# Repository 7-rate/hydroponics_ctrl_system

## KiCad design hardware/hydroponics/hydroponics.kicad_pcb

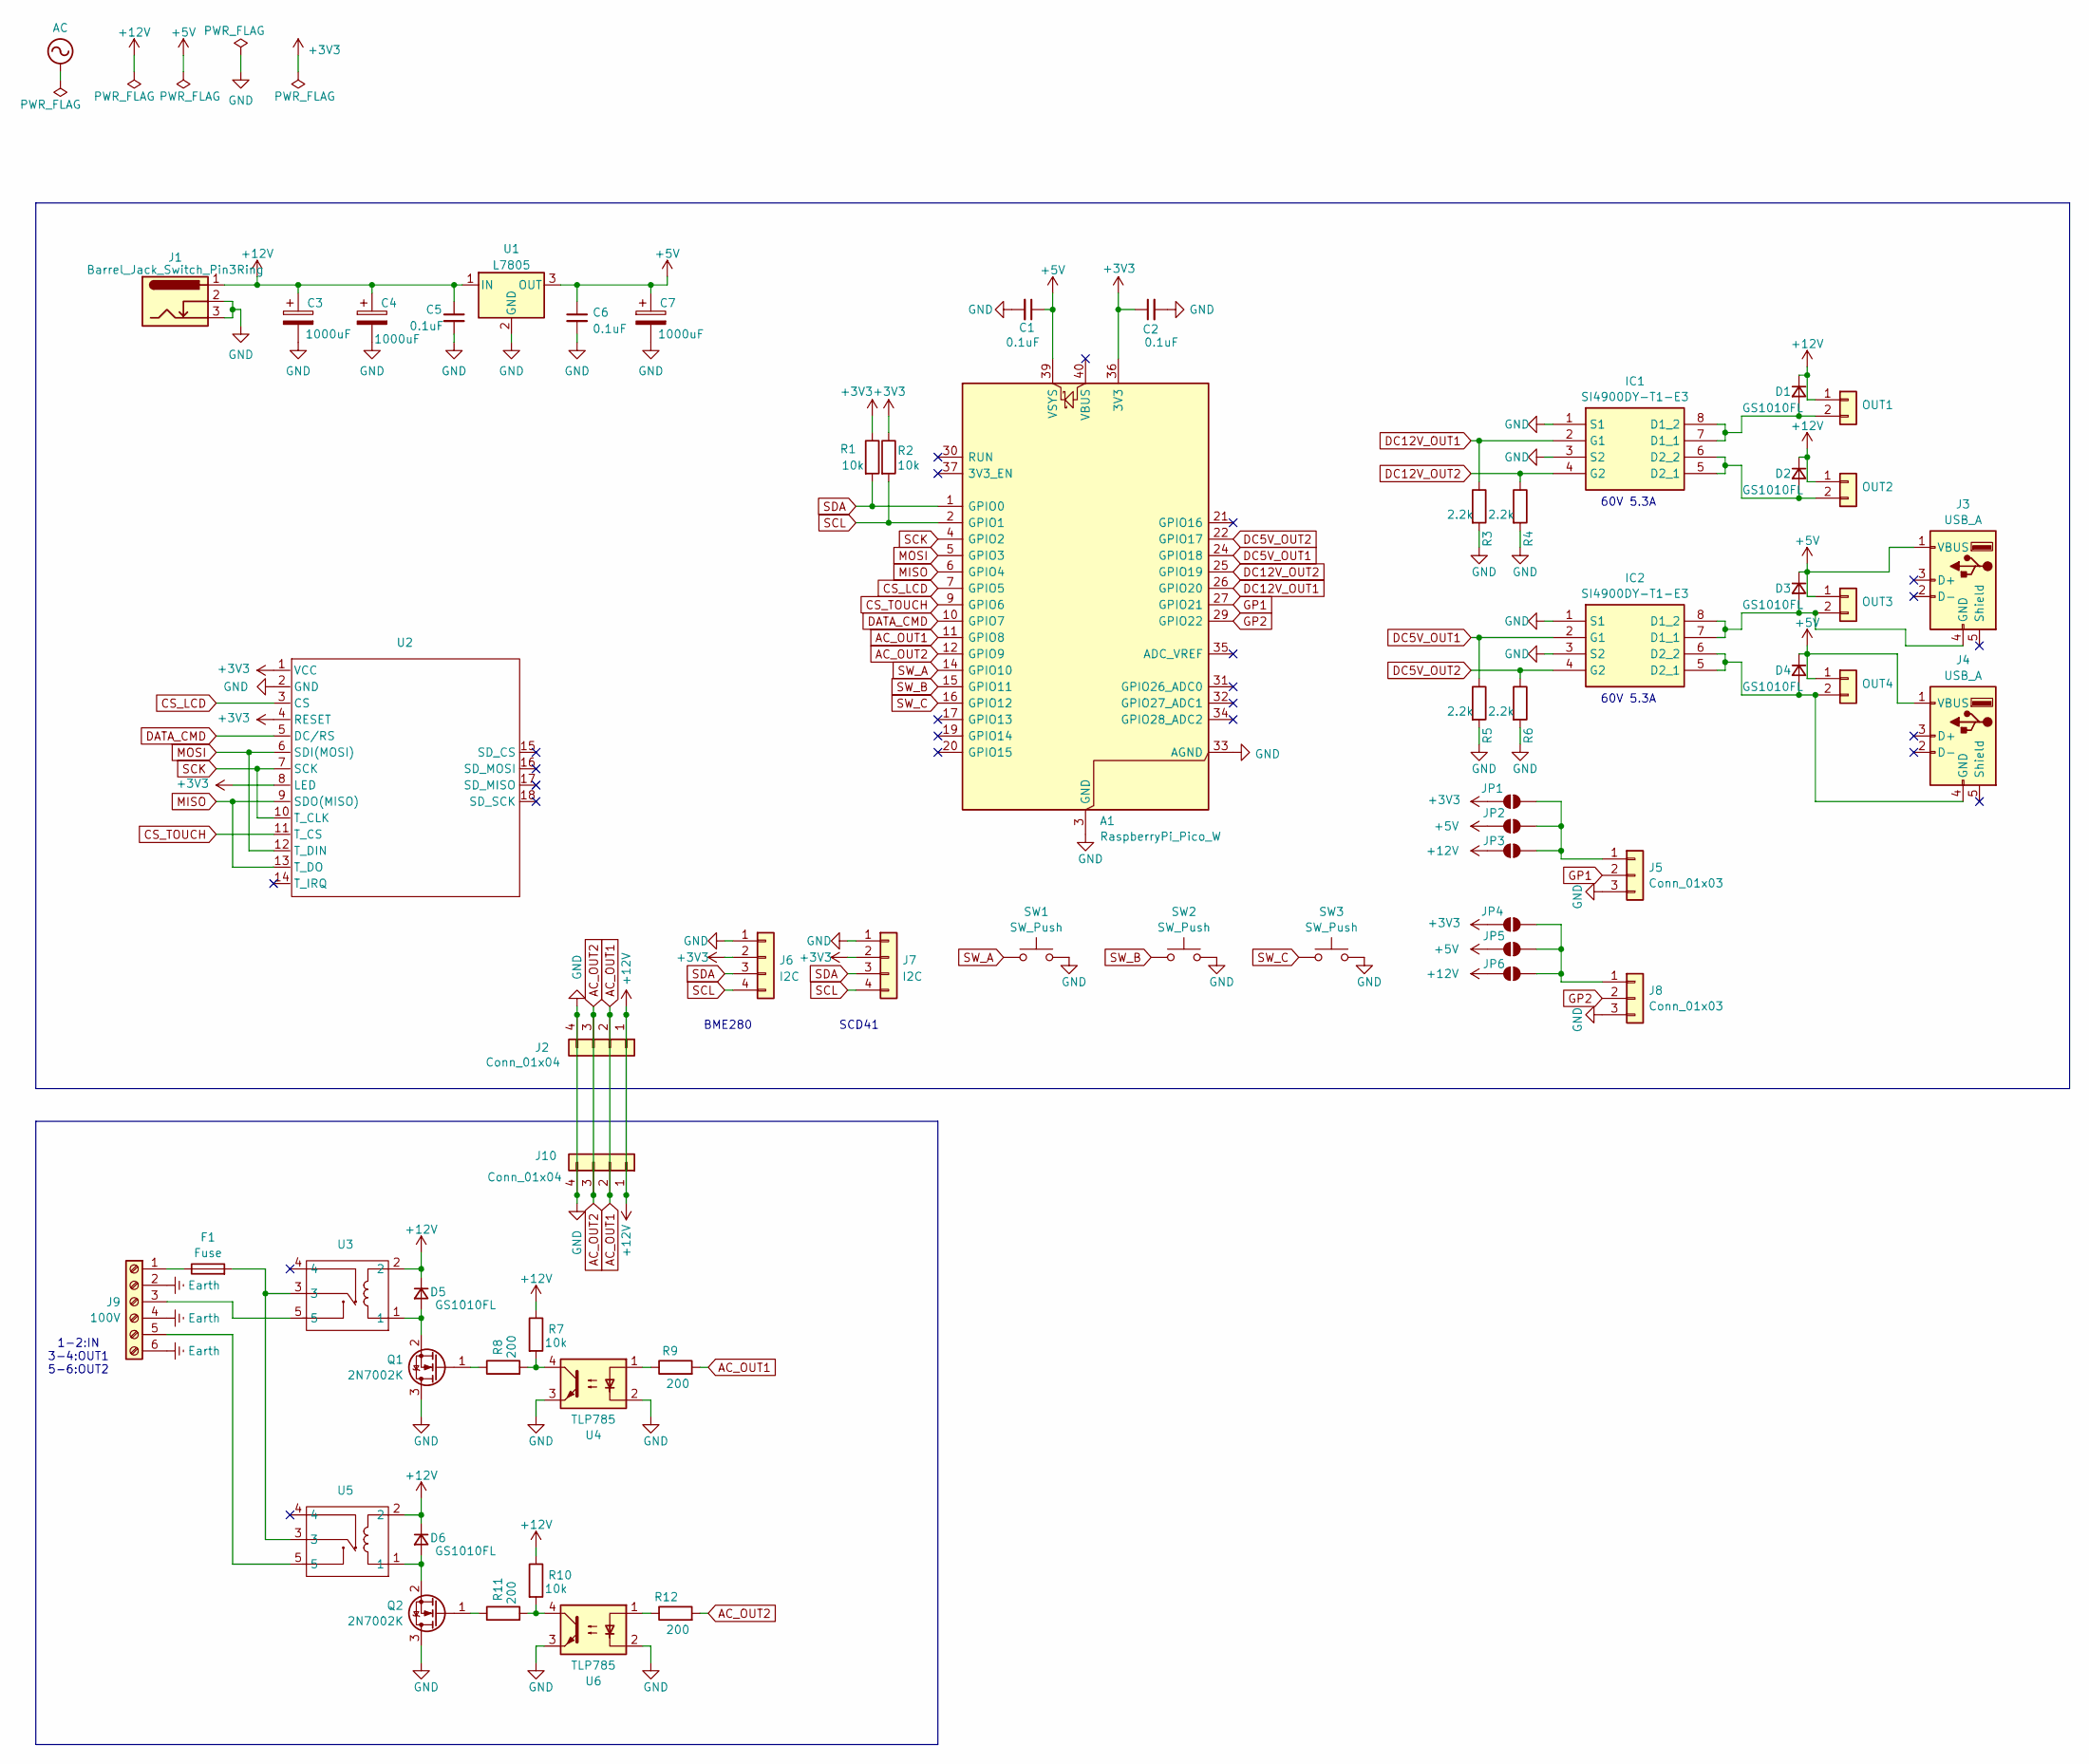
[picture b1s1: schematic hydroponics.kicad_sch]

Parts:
A1: RaspberryPi_Pico_W; RaspberryPi_Pico_W_SMD_HandSolder
C1, C2, C5, C6: 0.1uF; C_0603_1608Metric_Pad1.08x0.95mm_HandSolder
C3, C4, C7: 1000uF; CP_Radial_D10.0mm_P5.00mm_P7.50mm
D1, D2, D3, D4, D5, D6: GS1010FL; D_SOD-123F
F1: Fuse; MF-563
IC1, IC2: SI4900DY-T1-E3; SOIC127P600X175-8N; Mouser Part Number 781-SI4900DY-E3
J1: Barrel_Jack_Switch_Pin3Ring; BarrelJack_Horizontal
J2, J10: Conn_01x04; JST_XH_B4B-XH-AM_1x04_P2.50mm_Vertical
J3, J4: USB_A; USB_A_CONNFLY_DS1095-WNR0
J5, J8: Conn_01x03; JST_XH_B3B-XH-AM_1x03_P2.50mm_Vertical
J6, J7: I2C; JST_XH_B4B-XH-AM_1x04_P2.50mm_Vertical
J9: 100V; ML-40-S1AXF-6P
JP1, JP2, JP3, JP4, JP5, JP6: SolderJumper-2_P1.3mm_Open_RoundedPad1.0x1.5mm
OUT1, OUT2, OUT3, OUT4: JST_XH_B2B-XH-AM_1x02_P2.50mm_Vertical
Q1, Q2: 2N7002K; SOT-23
R1, R2, R7, R10: 10k; R_0603_1608Metric_Pad0.98x0.95mm_HandSolder
R3, R4, R5, R6: 2.2k; R_0603_1608Metric_Pad0.98x0.95mm_HandSolder
R8, R9, R11, R12: 200; R_0603_1608Metric_Pad0.98x0.95mm_HandSolder
SW1, SW2, SW3: SW_Push; SW_PUSH_6mm
U1: L7805; TO-252-2
U2: MSP2807
U3, U5: 943-1C-12DS
U4, U6: TLP785; DIP-4_W7.62mm

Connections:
+3V3: A1.36 (3V3), C2.1, J6.2, J7.2, JP1.1 (A), JP4.1 (A), R1.1, R2.1, U2.1 (VCC), U2.4 (RESET), U2.8 (LED)
+5V: A1.39 (VSYS), C1.1, C6.1, C7.1, D3.1 (K), D4.1 (K), J3.1 (VBUS), J4.1 (VBUS), JP2.1 (A), JP5.1 (A), OUT3.1, OUT4.1, U1.3 (OUT)
+12V: C3.1, C4.1, C5.1, D1.1 (K), D2.1 (K), D5.1 (K), D6.1 (K), J1.1, J2.1, J10.1, JP3.1 (A), JP6.1 (A), OUT1.1, OUT2.1, R7.1, R10.1, U1.1 (IN), U3.2, U5.2
AC_OUT1: A1.11 (GPIO8), J2.2, J10.2, R9.2
AC_OUT2: A1.12 (GPIO9), J2.3, J10.3, R12.2
CS_LCD: A1.7 (GPIO5), U2.3 (CS)
CS_TOUCH: A1.9 (GPIO6), U2.11 (T_CS)
DATA_CMD: A1.10 (GPIO7), U2.5 (DC/RS)
DC5V_OUT1: A1.24 (GPIO18), IC2.2 (G1), R5.1
DC5V_OUT2: A1.22 (GPIO17), IC2.4 (G2), R6.1
DC12V_OUT1: A1.26 (GPIO20), IC1.2 (G1), R3.1
DC12V_OUT2: A1.25 (GPIO19), IC1.4 (G2), R4.1
Earth: J9.2, J9.4, J9.6
GND: A1.3 (GND), A1.8 (GND), A1.13 (GND), A1.18 (GND), A1.23 (GND), A1.28 (GND), A1.33 (AGND), A1.38 (GND), C1.2, C2.2, C3.2, C4.2, C5.2, C6.2, C7.2, IC1.1 (S1), IC1.3 (S2), IC2.1 (S1), IC2.3 (S2), J1.2, J1.3, J2.4, J5.3, J6.1, J7.1, J8.3, J10.4, Q1.3 (D), Q2.3 (D), R3.2, R4.2, R5.2, R6.2, SW1.2, SW2.2, SW3.2, U1.2 (GND), U2.2 (GND), U4.2, U4.3, U6.2, U6.3
GP1: A1.27 (GPIO21), J5.2
GP2: A1.29 (GPIO22), J8.2
MISO: A1.6 (GPIO4), U2.9 (SDO(MISO)), U2.13 (T_DO)
MOSI: A1.5 (GPIO3), U2.6 (SDI(MOSI)), U2.12 (T_DIN)
unnamed: D1.2 (A), IC1.7 (D1_1), IC1.8 (D1_2), OUT1.2
unnamed: D2.2 (A), IC1.5 (D2_1), IC1.6 (D2_2), OUT2.2
unnamed: D3.2 (A), IC2.7 (D1_1), IC2.8 (D1_2), J3.4 (GND), OUT3.2
unnamed: D4.2 (A), IC2.5 (D2_1), IC2.6 (D2_2), J4.4 (GND), OUT4.2
unnamed: D5.2 (A), Q1.2 (S), U3.1
unnamed: D6.2 (A), Q2.2 (S), U5.1
unnamed: F1.2, U3.3, U5.3
unnamed: J5.1, JP1.2 (B), JP2.2 (B), JP3.2 (B)
unnamed: J8.1, JP4.2 (B), JP5.2 (B), JP6.2 (B)
unnamed: F1.1, J9.1
unnamed: J9.3, U3.5
unnamed: J9.5, U5.5
unnamed: Q1.1 (G), R8.1
unnamed: Q2.1 (G), R11.1
unnamed: R7.2, R8.2, U4.4
unnamed: R9.1, U4.1
unnamed: R10.2, R11.2, U6.4
unnamed: R12.1, U6.1
SCK: A1.4 (GPIO2), U2.7 (SCK), U2.10 (T_CLK)
SCL: A1.2 (GPIO1), J6.4, J7.4, R2.2
SDA: A1.1 (GPIO0), J6.3, J7.3, R1.2
SW_A: A1.14 (GPIO10), SW1.1
SW_B: A1.15 (GPIO11), SW2.1
SW_C: A1.16 (GPIO12), SW3.1

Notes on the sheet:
60V 5.3A
1-2:IN 3-4:OUT1 5-6:OUT2
SCD41
BME280

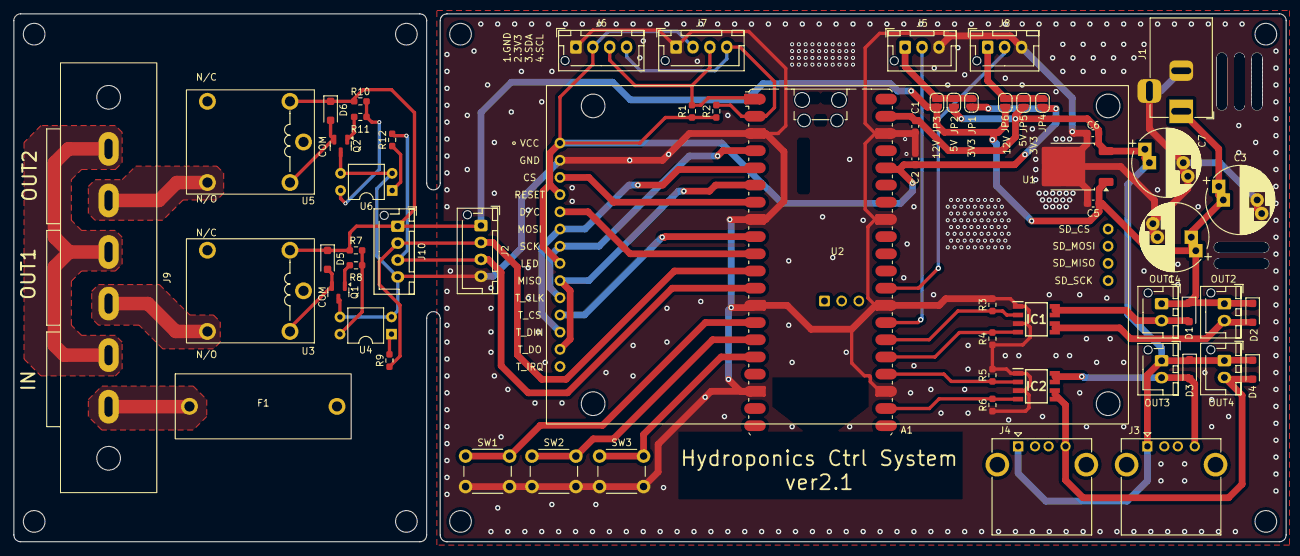
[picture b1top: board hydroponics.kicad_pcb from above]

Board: 2 copper layers, 188.0 x 78.0 mm, 60 parts (0 on the bottom side), 42 nets.

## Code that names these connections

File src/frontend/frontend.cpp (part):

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/* Local definitions               */
/***********************************/
// SPI Pin Definitions for Display
#define PIN_SCK 2  // GPIO2
#define PIN_MOSI 3 // GPIO3
#define PIN_MISO 4 // GPIO4
#define PIN_CS 5   // GPIO5
#define PIN_DC 7   // GPIO6 for DC (Data/Command)
#define PIN_RST -1 // GPIO7 for Reset

// Touch Controller Pin
#define PIN_TOUCH_CS 6 // GPIO8 for Touch Controller CS

class toggle_button {
  public:
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
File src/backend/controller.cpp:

/*
 * 概要：各ポートの制御を行うクラス
 */
#include <Arduino.h>

#include "controller.h"

/******************************************************************/
/* Definitions                                                    */
/******************************************************************/
/***********************************/
/* Local definitions               */
/***********************************/
#define AC_OUT1 ( 8 )
#define AC_OUT2 ( 9 )
#define DC12V_OUT1 ( 20 )
#define DC12V_OUT2 ( 19 )
#define DC5V_OUT1 ( 18 )
#define DC5V_OUT2 ( 17 )

/***********************************/
/* Local Variables                 */
/***********************************/
static ac_state_t AC_OUT1_state = AC_OFF;
static ac_state_t AC_OUT2_state = AC_OFF;
static int DC12V_OUT1_state = 0;
static int DC12V_OUT2_state = 0;
static int DC5V_OUT1_state = 0;
static int DC5V_OUT2_state = 0;

/***********************************/
/* Global Variables                */
/***********************************/

/******************************************************************/
/* Implementation                                                 */
/******************************************************************/
/***********************************/
/* Local functions                 */
/***********************************/
static PinStatus ac_pin_status( ac_state_t state ) {
    return ( state == AC_ON ) ? HIGH : LOW;
}

/***********************************/
/* Class implementions             */
/***********************************/

/***********************************/
/* Global functions                */
/***********************************/
void controller_set_AC_OUT1( ac_state_t state ) {
    AC_OUT1_state = state;
    digitalWrite( AC_OUT1, ac_pin_status( AC_OUT1_state ) );
}

void controller_set_AC_OUT2( ac_state_t state ) {
    AC_OUT2_state = state;
    digitalWrite( AC_OUT2, ac_pin_status( AC_OUT2_state ) );
}

void controller_set_DC12V_OUT1( dc_state_t state ) {
    int value = 0;
    switch ( state ) {
    case DC_ON:
        value = 255;
        break;
    case DC_F1_FLUCT:
        value = 127; // TODO 1/f揺らぎの実装
        break;
    case DC_OFF:
    default:
        value = 0;
        break;
    }
    DC12V_OUT1_state = value;
    analogWrite( DC12V_OUT1, DC12V_OUT1_state );
}

void controller_set_DC12V_OUT2( dc_state_t state ) {
    int value = 0;
    switch ( state ) {
    case DC_ON:
        value = 255;
        break;
    case DC_F1_FLUCT:
        value = 127; // TODO 1/f揺らぎの実装
        break;
    case DC_OFF:
    default:
        value = 0;
        break;
    }
    DC12V_OUT2_state = value;
    analogWrite( DC12V_OUT2, DC12V_OUT2_state );
}

void controller_set_DC5V_OUT1( dc_state_t state ) {
    int value = 0;
    switch ( state ) {
    case DC_ON:
        value = 255;
        break;
    case DC_F1_FLUCT:
        value = 127; // TODO 1/f揺らぎの実装
        break;
    case DC_OFF:
    default:
        value = 0;
        break;
    }
    DC5V_OUT1_state = value;
    analogWrite( DC5V_OUT1, DC5V_OUT1_state );
}

void controller_set_DC5V_OUT2( dc_state_t state ) {
    int value = 0;
    switch ( state ) {
    case DC_ON:
        value = 255;
        break;
    case DC_F1_FLUCT:
        value = 127; // TODO 1/f揺らぎの実装
        break;
    case DC_OFF:
    default:
        value = 0;
        break;
    }
    DC5V_OUT2_state = value;
    analogWrite( DC5V_OUT2, DC5V_OUT2_state );
}

void controller_init( void ) {
    pinMode( AC_OUT1, OUTPUT );
    pinMode( AC_OUT2, OUTPUT );
    pinMode( DC12V_OUT1, OUTPUT );
    pinMode( DC12V_OUT2, OUTPUT );
    pinMode( DC5V_OUT1, OUTPUT );
    pinMode( DC5V_OUT2, OUTPUT );

    digitalWrite( AC_OUT1, HIGH );
    digitalWrite( AC_OUT2, HIGH );
    analogWrite( DC12V_OUT1, 0 );
    analogWrite( DC12V_OUT2, 0 );
    analogWrite( DC5V_OUT1, 0 );
    analogWrite( DC5V_OUT2, 0 );
}

void controller_task() {
}

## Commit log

2025-04-16 TFT_test
2025-04-16 不要機能削除
2025-04-16 ハードウェアデータ追加
2025-04-20 一旦コミット
2025-04-20 UI修正
2025-04-20 タッチスクリーン補正とバックエンドへのつなぎを作成
2025-04-20 スケジューラー作成(途中)
